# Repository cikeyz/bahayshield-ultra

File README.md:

# BahayShield ULTRA

<p align="center">
  <strong>Offline flood and typhoon preparedness controller for a tabletop home-safety demo.</strong><br>
  Arduino Mega 2560 Pro · HC-SR04 · BME280 · TRI scoring · low-voltage relay cut
</p>

<p align="center">
  <a href="#overview">Overview</a>
  &nbsp;·&nbsp;
  <a href="#features">Features</a>
  &nbsp;·&nbsp;
  <a href="#gallery">Gallery</a>
  &nbsp;·&nbsp;
  <a href="#quick-start">Quick Start</a>
  &nbsp;·&nbsp;
  <a href="#project-structure">Structure</a>
  &nbsp;·&nbsp;
  <a href="#license">License</a>
</p>

## Contents

- [Overview](#overview)
- [Features](#features)
- [System architecture](#system-architecture)
- [Hardware](#hardware)
- [Firmware](#firmware)
- [Gallery](#gallery)
- [Quick Start](#quick-start)
- [Project Structure](#project-structure)
- [Safety](#safety)
- [License](#license)
- [Course Note](#course-note)

## Overview

BahayShield ULTRA is an offline microcontroller system that combines ultrasonic water-level sensing with barometric pressure trend analysis. It computes a Typhoon Risk Index (TRI), stages visual and audible alerts, and can open a low-voltage demo load through a relay when risk stays high long enough.

The demo unit pairs a control enclosure with a house diorama and clear flood tray. It is a tabletop simulation, not a field-installed household electrical product, and it does not switch AC mains.

**Controller:** final build uses an **Arduino Mega 2560 Pro** compact module (ATmega2560, CH340 USB, dual-row 100-mil headers). Early breadboard work may use a full-size Mega 2560 form factor; the MCU and IDE board target stay the same (`Arduino Mega or Mega 2560`).

## Features

| Feature | Description |
|---------|-------------|
| Water level | HC-SR04 over a fixed mast; mapped to dry / ankle / knee / waist / critical |
| Barometric trend | BME280 pressure feeds rolling slope and baseline into TRI |
| Storm profiles | Habagat, Bagyo, and Flash Flood reweight water vs pressure |
| Staged alerts | LED bar, alert LED, buzzer cadence, 20x4 LCD |
| Relay cut | Relay 1 COM-NC on a 5 V demo load; active-LOW coil drive |
| Operator inputs | PCF8574 4x4 keypad, A1 button ladder, serial commands |
| Event log | DS3231 timebase + AT24C32 EEPROM with checksummed records |
| Mechanical stack | KiCad motherboard project, 3D-printed enclosure, HC-SR04 mast |

## System architecture

```mermaid
flowchart LR
  subgraph Inputs
    US[HC-SR04]
    BME[BME280]
    POT[A0 pressure pot]
    BTN[Buttons]
    KEY[Keypad]
  end

  subgraph Controller
    MCU[Mega 2560 Pro<br/>ATmega2560<br/>TRI + FSM]
    RTC[DS3231 RTC]
    PWR[XL4015 5 V rail]
  end

  subgraph Outputs
    LED[TRI LEDs + alert]
    BUZ[Active buzzer]
    REL[Relay 1 COM-NC<br/>5 V load]
    LCD[20x4 I2C LCD]
    LOG[AT24C32 event log]
  end

  US --> MCU
  BME --> MCU
  POT --> MCU
  BTN --> MCU
  KEY --> MCU
  RTC --> MCU
  PWR --> MCU
  MCU --> LED
  MCU --> BUZ
  MCU --> REL
  MCU --> LCD
  MCU --> LOG
```

Editable diagrams: [`docs/diagrams/`](docs/diagrams/).  
Deeper write-up: [`docs/overview.md`](docs/overview.md).

## Hardware

| Block | Part | Role |
|-------|------|------|
| MCU | Arduino Mega 2560 Pro (ATmega2560) | Final controller; 5 V on `5V` pin (`VIN` unused) |
| Water | HC-SR04 | Distance over diorama tray |
| Environment | BME280 (I2C, typically `0x76`) | Pressure for TRI; temp/humidity for display only |
| RTC + log | DS3231 + AT24C32 | Timekeeping and event log |
| Display | 20x4 I2C LCD (primary `0x27`) | TRI, profile, water, pressure, state |
| Keypad | 4x4 via PCF8574 (`0x20`) | Profile, mute, cut, ack, page |
| Buttons | 3x tactile on A1 ladder | Yellow cut, Blue view, Green ack |
| Indicators | 5 TRI LEDs + alert LED + buzzer | Staged alert UI |
| Actuator | 2-ch 5 V relay module | Relay 1 demo-load cut; Relay 2 spare |
| Power | USB-C PD source → XL4015 buck → 5.00 V | Fuse + reverse protection on the design |
| Load | 5 V LED strip on Relay 1 COM-NC | Stand-in for a ground-floor branch |
| PCB | KiCad Rev A motherboard | Headers for Mega 2560 Pro and modules |
| Enclosure | Printed base, top panel, BME280 cage, mast | Control unit + sensor geometry |

- Pin map: [`hardware/pinout.md`](hardware/pinout.md)
- Power path: [`hardware/power-tree.md`](hardware/power-tree.md)
- BOM: [`hardware/bom.md`](hardware/bom.md)
- Wiring: [`hardware/wiring-overview.md`](hardware/wiring-overview.md)
- PCB project: [`pcb/`](pcb/)
- Enclosure STLs: [`enclosure/`](enclosure/)

## Firmware

Production sketch: [`firmware/bahayshield-ultra/`](firmware/bahayshield-ultra/)

- Non-blocking `millis()` scheduler
- Fixed-point TRI suited to Mega-class SRAM
- Non-blocking HC-SR04 echo state machine
- Active-LOW relay with confirm window before power-cut latch
- Serial at `115200` baud

Bring-up suite: [`firmware/bring-up/`](firmware/bring-up/) (I2C, LCD, keypad, RTC, BME280, relay, ultrasonic, full breadboard integration).

Libraries for production:

```text
Wire
Adafruit BME280
Adafruit Unified Sensor
Adafruit BusIO
```

LCD and PCF8574 keypad use direct `Wire` access.

## Gallery

| Mega 2560 Pro (front) | Mega 2560 Pro (back) |
|-----------------------|----------------------|
|  |  |

| BME280 | DS3231 + AT24C32 | XL4015 buck |
|--------|-----------------|-------------|
|  |  |  |

| Serial: upload OK | Serial: HC-SR04 |
|-------------------|-----------------|
|  |  |

| Serial: keypad | Serial: LCD I2C |
|----------------|-----------------|
|  |  |

Full set: [`docs/photos/`](docs/photos/).

## Quick Start

```bash
git clone https://github.com/cikeyz/bahayshield-ultra.git
cd bahayshield-ultra
```

1. Install Arduino IDE or Arduino CLI.
2. Select board **Arduino Mega or Mega 2560** (ATmega2560 on the Mega 2560 Pro module).
3. Install Adafruit BME280 and its dependencies.
4. Open `firmware/bahayshield-ultra/bahayshield-ultra.ino`.
5. Upload with the external load disconnected.
6. Open Serial Monitor at `115200`. Confirm I2C devices, LCD, and inactive relay before connecting the LED-strip load path.

| Cmd | Action |
|-----|--------|
| `c` | Manual relay cut |
| `a` | Acknowledge / reset when safe |
| `v` | Cycle LCD page |
| `m` | Mute buzzer |
| `1` / `2` / `3` | Habagat / Bagyo / Flash Flood |
| `?` | Help |

Demo script: [`docs/demo-procedure.md`](docs/demo-procedure.md).

## Project Structure

```text
bahayshield-ultra/
├── README.md
├── LICENSE
├── .gitignore
├── firmware/
│   ├── bahayshield-ultra/     # production sketch
│   └── bring-up/              # M00-M16 driver tests
├── hardware/
│   ├── pinout.md
│   ├── power-tree.md
│   ├── bom.md
│   └── wiring-overview.md
├── pcb/
│   ├── README.md
│   ├── rev-a/                 # KiCad Rev A + local libraries
│   └── archive/prototype-1/   # early routing baseline
├── enclosure/
│   ├── README.md
│   ├── scad/
│   └── stl/
└── docs/
    ├── overview.md
    ├── demo-procedure.md
    ├── diagrams/
    └── photos/
```

## Safety

- Relay contacts switch a **5 V demo load** only. No AC, outlets, extension cords, or household branch wiring.
- Humidity and temperature are display/log context. Pressure is the barometric input to TRI and cutoff logic.
- Storm demos can use the A0 potentiometer for a repeatable pressure curve while BME280 still reports real ambient pressure.
- Verify buck output at 5.00 V, relay active level, and COM-NC continuity before a live demo.

## License

MIT. See [LICENSE](LICENSE).

## Course Note

Built for CMPE 311 (Microprocessor Systems), Polytechnic University of the Philippines, Group 4, A.Y. 2025-2026, under Engr. Rufo I. Marasigan Jr., D.Eng, PCpE. Published here as a standalone project.

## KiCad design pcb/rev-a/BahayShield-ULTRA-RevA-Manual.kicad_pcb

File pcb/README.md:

# PCB

## Rev A

Path: [`rev-a/`](rev-a/)

KiCad motherboard for BahayShield ULTRA. It sockets an **Arduino Mega 2560 Pro** on 100-mil headers and brings out I2C modules, relay logic, load path, indicators, and power protection.

```text
pcb/rev-a/BahayShield-ULTRA-RevA-Manual.kicad_pro
```

Local symbol and footprint libraries: `rev-a/libraries/`.

### Status

- Schematic covers the intended nets: MCU headers, I2C, relay inputs, load terminals, protection, bulk caps, TRI LEDs, buzzer drive.
- Before ordering boards, re-run ERC/DRC on your KiCad version, confirm relay header order (`GND IN1 IN2 VCC`) and contact group (`NO COM NC`) against the module you hold, and check keep-outs against the printed enclosure.
- This tree is a design package, not a certified production Gerber drop.

## Prototype-1 (archive)

Path: [`archive/prototype-1/`](archive/prototype-1/)

Early low-voltage routing baseline. Kept for history. Prefer Rev A for current pin and feature set.

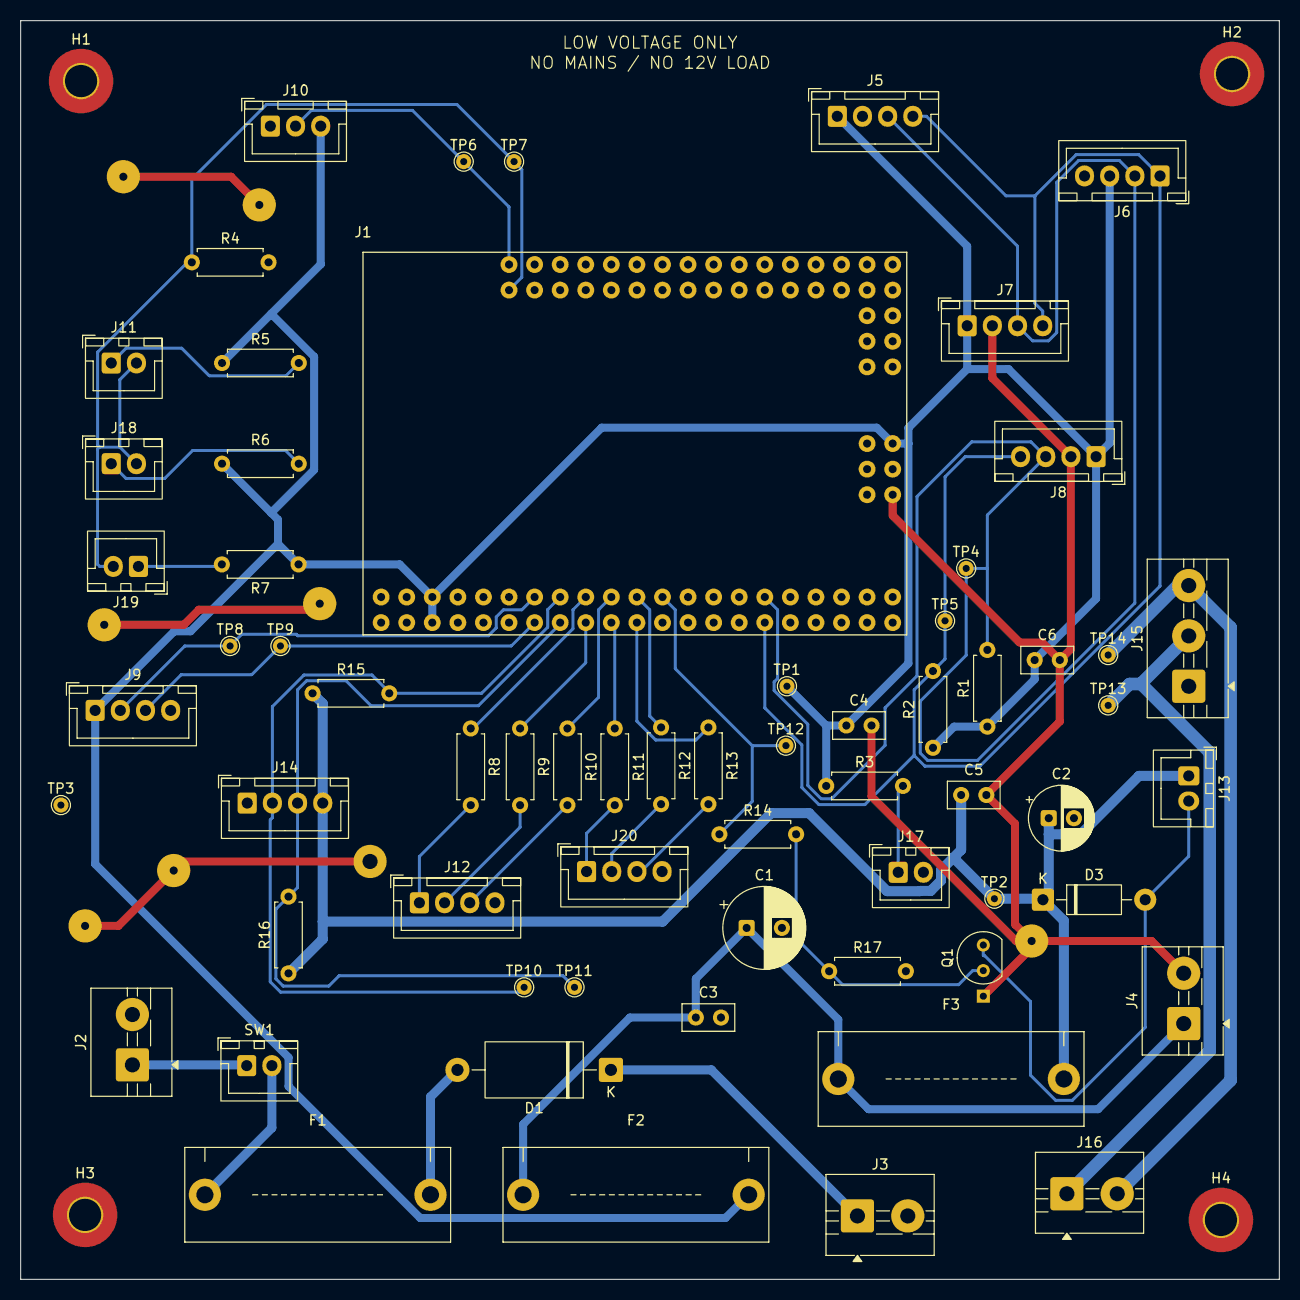
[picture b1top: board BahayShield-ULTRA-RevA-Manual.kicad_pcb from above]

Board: 2 copper layers, 125.0 x 125.0 mm, 68 parts (0 on the bottom side), 37 nets.

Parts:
C1: 470u_25V_MAIN_5V_BULK; CP_Radial_D8.0mm_P3.50mm
C2: 100u_ACT_BULK; CP_Radial_D6.3mm_P2.50mm
C3: 100n_5V_MAIN_CERAMIC; C_Disc_D5.0mm_W2.5mm_P2.50mm
C4: 100n_LOGIC_CERAMIC; C_Disc_D5.0mm_W2.5mm_P2.50mm
C5: 100n_RELAY_ACT_CERAMIC; C_Disc_D5.0mm_W2.5mm_P2.50mm
C6: 100n_I2C_SENSOR_CERAMIC; C_Disc_D5.0mm_W2.5mm_P2.50mm
D1: 1N5822_REVERSE_PROTECTION; D_DO-27_P15.24mm_Horizontal
D3: 1N4007_BUZZER_CLAMP; D_DO-41_SOD81_P10.16mm_Horizontal
F1: F1A_INPUT_FUSE_5X20; Fuseholder_5x20mm_TwoProng_P22.40mm_Drill1.70mm
F2: F1A_LOGIC_BRANCH; Fuseholder_5x20mm_TwoProng_P22.40mm_Drill1.70mm
F3: F2A_ACTUATOR_BRANCH; Fuseholder_5x20mm_TwoProng_P22.40mm_Drill1.70mm
H1, H2, H3, H4: MountingHole_3.2mm_M3_Pad_TopBottom
J1: MEGA_PRO_EMBED_CH340G___ATMEGA2560; MODULE_MEGA_PRO_EMBED_CH340G___ATMEGA2560
J2: PD_BARREL_OR_PANEL_DC_IN; KF301-5.0-02P_1x02_P5.00mm_Drill1.50mm_Pad3.30mm
J3: PCB_TO_XL4015_INPUT; KF301-5.0-02P_1x02_P5.00mm_Drill1.50mm_Pad3.30mm
J4: XL4015_OUTPUT_TO_PCB_5V00; KF301-5.0-02P_1x02_P5.00mm_Drill1.50mm_Pad3.30mm
J5: 20X4_LCD_I2C_PANEL; JST_XH_B4B-XH-A_1x04_P2.50mm_Vertical_Drill1.10mm
J6: DS3231_AT24C32_MODULE_XH4; JST_XH_B4B-XH-A_1x04_P2.50mm_Vertical_Drill1.10mm
J7: BME280_5V_APPROVED_XH4; JST_XH_B4B-XH-A_1x04_P2.50mm_Vertical_Drill1.10mm
J8: PCF8574_KEYPAD_EXPANDER_XH4; JST_XH_B4B-XH-A_1x04_P2.50mm_Vertical_Drill1.10mm
J9: DIORAMA_HC_SR04_MAST_XH4; JST_XH_B4B-XH-A_1x04_P2.50mm_Vertical_Drill1.10mm
J10: A0_PRESSURE_SIM_10K_XH3; JST_XH_B3B-XH-A_1x03_P2.50mm_Vertical_Drill1.10mm
J11: PANEL_BTN1_MANUAL_CUT_XH2; JST_XH_B2B-XH-A_1x02_P2.50mm_Vertical_Drill1.10mm
J12: PANEL_STATUS_LEDS_G1_G2_Y_XH4; JST_XH_B4B-XH-A_1x04_P2.50mm_Vertical_Drill1.10mm
J13: ACTIVE_BUZZER_5V_XH2; JST_XH_B2B-XH-A_1x02_P2.50mm_Vertical_Drill1.10mm
J14: 2CH_RELAY_MODULE_INPUT_GND_IN1_IN2_VCC_XH4; JST_XH_B4B-XH-A_1x04_P2.50mm_Vertical_Drill1.10mm
J15: RELAY1_CONTACT_NO_COM_NC; KF301-5.0-03P_1x03_P5.00mm_Drill1.50mm_Pad3.30mm
J16: LOW_VOLTAGE_DEMO_LOAD; KF301-5.0-02P_1x02_P5.00mm_Drill1.50mm_Pad3.30mm
J17: PANEL_POWER_LED_XH2; JST_XH_B2B-XH-A_1x02_P2.50mm_Vertical_Drill1.10mm
J18: PANEL_BTN2_VIEW_XH2; JST_XH_B2B-XH-A_1x02_P2.50mm_Vertical_Drill1.10mm
J19: PANEL_BTN3_ACK_RESET_XH2; JST_XH_B2B-XH-A_1x02_P2.50mm_Vertical_Drill1.10mm
J20: PANEL_ALERT_LEDS_O_R_ALERT_XH4; JST_XH_B4B-XH-A_1x04_P2.50mm_Vertical_Drill1.10mm
Q1: 2N2222_BUZZER_LOW_SIDE_EBC; TO-92_Inline
R1: 4.7k_SDA_PULLUP; R_Axial_DIN0207_L6.3mm_D2.5mm_P7.62mm_Horizontal
R2: 4.7k_SCL_PULLUP; R_Axial_DIN0207_L6.3mm_D2.5mm_P7.62mm_Horizontal
R3: 1k_POWER_LED; R_Axial_DIN0207_L6.3mm_D2.5mm_P7.62mm_Horizontal
R4: 10k_A1_PULLDOWN; R_Axial_DIN0207_L6.3mm_D2.5mm_P7.62mm_Horizontal
R5: 1k_BTN_MANUAL_CUT; R_Axial_DIN0207_L6.3mm_D2.5mm_P7.62mm_Horizontal
R6: 2.2k_BTN_VIEW; R_Axial_DIN0207_L6.3mm_D2.5mm_P7.62mm_Horizontal
R7: 4.7k_BTN_ACK_RESET; R_Axial_DIN0207_L6.3mm_D2.5mm_P7.62mm_Horizontal
R8: 330_LED_G1; R_Axial_DIN0207_L6.3mm_D2.5mm_P7.62mm_Horizontal
R9: 330_LED_G2; R_Axial_DIN0207_L6.3mm_D2.5mm_P7.62mm_Horizontal
R10: 330_LED_Y; R_Axial_DIN0207_L6.3mm_D2.5mm_P7.62mm_Horizontal
R11: 330_LED_O; R_Axial_DIN0207_L6.3mm_D2.5mm_P7.62mm_Horizontal
R12: 330_LED_R; R_Axial_DIN0207_L6.3mm_D2.5mm_P7.62mm_Horizontal
R13: 330_LED_ALERT; R_Axial_DIN0207_L6.3mm_D2.5mm_P7.62mm_Horizontal
R14: 1k_BUZZER_BASE; R_Axial_DIN0207_L6.3mm_D2.5mm_P7.62mm_Horizontal
R15: 10k_RELAY1_IN_PULLUP_SAFE_OFF; R_Axial_DIN0207_L6.3mm_D2.5mm_P7.62mm_Horizontal
R16: 10k_RELAY2_IN_PULLUP_SAFE_OFF; R_Axial_DIN0207_L6.3mm_D2.5mm_P7.62mm_Horizontal
R17: 100k_BUZZER_BASE_PULLDOWN; R_Axial_DIN0207_L6.3mm_D2.5mm_P7.62mm_Horizontal
SW1: KCD11_MAIN_SWITCH_HARNESS; JST_XH_B2B-XH-A_1x02_P2.50mm_Vertical_Drill1.10mm
TP1, TP2, TP3, TP4, TP5, TP6, TP7, TP8, TP9, TP10, TP11, TP12, TP13, TP14: TestPoint; TestPoint_THTPad_D1.5mm_Drill0.7mm

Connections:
5V: C4.1, C6.1, F2.2, J1.5V_1 (5V), J1.5V_2 (5V), J1.5V_3 (5V), J5.1, J6.3, J7.1, J8.1, J9.1, J10.3, R1.1, R2.1, R3.1, R5.1, R6.1, R7.1, TP1.1 (1_1)
/+5V_ACT: C2.1, C5.1, D3.1 (K), F3.2, J13.1, J14.4, R15.1, R16.1, TP2.1 (1_1)
/+5V_BUCK: C1.1, C3.1, F2.1, F3.1, J4.1
/A0_PRESSURE: J1.A0, J10.2, TP6.1 (1_1)
/A1_BUTTONS: J1.A1, J11.2, J18.2, J19.2, R4.1, TP7.1 (1_1)
/BTN1_SRC: J11.1, R5.2
/BTN2_SRC: J18.1, R6.2
/BTN3_SRC: J19.1, R7.2
/BUZZER_BASE: Q1.2 (B), R14.2, R17.1
/BUZZER_NEG: D3.2 (A), J13.2, Q1.3 (C)
/D6_LED_G1: J1.D6, R8.1
/D7_LED_G2: J1.D7, R9.1
/D8_LED_Y: J1.D8, R10.1
/D9_LED_O: J1.D9, R11.1
/D10_LED_R: J1.D10, R12.1
/D11_LED_ALERT: J1.D11, R13.1
/D12_BUZZER: J1.D12, R14.1, TP12.1 (1_1)
/LED_ALERT: J20.3, R13.2
/LED_TRI_G1: J12.1, R8.2
/LED_TRI_G2: J12.2, R9.2
/LED_TRI_O: J20.1, R11.2
/LED_TRI_R: J20.2, R12.2
/LED_TRI_Y: J12.3, R10.2
/LOAD_IN: J15.2, J16.1, TP13.1 (1_1)
/LOAD_OUT: J15.3, J16.2, TP14.1 (1_1)
/PWR_LED_A: J17.1, R3.2
/RELAY1_IN: J1.D4, J14.2, R15.2, TP10.1 (1_1)
/RELAY2_IN: J1.D5, J14.3, R16.2, TP11.1 (1_1)
/SCL: J1.D21, J5.4, J6.1, J7.4, J8.4, R2.2, TP5.1 (1_1)
/SDA: J1.D20, J5.3, J6.2, J7.3, J8.3, R1.2, TP4.1 (1_1)
/US_ECHO: J1.D3, J9.3, TP9.1 (1_1)
/US_TRIG: J1.D2, J9.2, TP8.1 (1_1)
/VIN_FUSED: D1.2 (A), F1.2
/VIN_PROTECTED: D1.1 (K), J3.1
/VIN_SRC: J2.1, SW1.1
/VIN_SW: F1.1, SW1.2
GND: C1.2, C2.2, C3.2, C4.2, C5.2, C6.2, J1.GND_1 (GND), J1.GND_2 (GND), J1.GND_3 (GND), J2.2, J3.2, J4.2, J5.2, J6.4, J7.2, J8.2, J9.4, J10.1, J12.4, J14.1, J17.2, J20.4, Q1.1 (E), R4.2, R17.2, TP3.1 (1_1)

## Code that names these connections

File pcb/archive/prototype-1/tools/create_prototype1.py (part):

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
COMPONENTS = [
    {"ref": "J1A", "value": "MEGA_PWR_I2C", "footprint": HEADER_4, "pos": (24, 16), "pins": ["+5V", "GND", "SDA", "SCL"]},
    {"ref": "J1B", "value": "MEGA_WATER_ACTUATOR", "footprint": HEADER_4, "pos": (24, 32), "pins": ["US_TRIG", "US_ECHO", "BUZZER", "RELAY1"]},
    {"ref": "J1C", "value": "MEGA_ALERTS", "footprint": HEADER_4, "pos": (24, 48), "pins": ["RELAY2", "LED_GREEN", "LED_YELLOW", "LED_RED"]},
    {"ref": "J1D", "value": "MEGA_ANALOG_POWER", "footprint": HEADER_4, "pos": (24, 64), "pins": ["A0_PRESSURE", "A1_BUTTONS", "+3V3", "GND"]},
    {"ref": "J1E", "value": "MEGA_SPARE_SERVICE", "footprint": HEADER_4, "pos": (24, 80), "pins": ["+5V", "GND", "NC_VIN", "NC_RESET"]},
    {"ref": "J2", "value": "LCD_I2C", "footprint": HEADER_4, "pos": (112, 14), "pins": ["+5V", "GND", "SDA", "SCL"]},
    {"ref": "J3", "value": "RTC_I2C", "footprint": HEADER_4, "pos": (112, 27), "pins": ["+5V", "GND", "SDA", "SCL"]},
    {"ref": "J4", "value": "KEYPAD_I2C", "footprint": HEADER_4, "pos": (112, 40), "pins": ["+5V", "GND", "SDA", "SCL"]},
    {"ref": "J5", "value": "BMP280_OPTION", "footprint": HEADER_4, "pos": (112, 53), "pins": ["+3V3", "GND", "SDA", "SCL"]},
    {"ref": "J6", "value": "DIORAMA_USONIC", "footprint": HEADER_4, "pos": (112, 66), "pins": ["+5V", "US_TRIG", "US_ECHO", "GND"]},
    {"ref": "J7", "value": "BTN_LADDER_A1", "footprint": HEADER_4, "pos": (56, 64), "pins": ["+5V", "A1_BUTTONS", "GND", "NC_BTN_SPARE"]},
    {"ref": "J8", "value": "PRESSURE_SIM_A0", "footprint": HEADER_4, "pos": (40, 64), "pins": ["A0_PRESSURE", "+5V", "GND", "NC_PRESSURE_SPARE"]},
    {"ref": "J9", "value": "RELAY_IN", "footprint": HEADER_4, "pos": (88, 48), "pins": ["RELAY2", "RELAY1", "+5V", "GND"]},
    {"ref": "J10", "value": "LOW_VOLTAGE_DEMO_LOAD", "footprint": TERM_2, "pos": (123, 78), "pins": ["LOAD_IN", "LOAD_OUT"]},
    {"ref": "J11", "value": "REGULATED_5V_IN", "footprint": TERM_2, "pos": (8, 80), "pins": ["+5V", "GND"]},
    {"ref": "J12", "value": "BUZZER_OUT", "footprint": HEADER_2, "pos": (56, 78), "pins": ["BUZZER", "GND"]},
    {"ref": "J13", "value": "STATUS_LEDS", "footprint": HEADER_4, "pos": (56, 48), "pins": ["LED_GREEN", "LED_YELLOW", "LED_RED", "GND"]},
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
